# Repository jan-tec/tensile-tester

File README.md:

# Tensile Tester

ESP32 firmware for a tensile test machine (Zugversuchsmaschine): a
gear-stepper spindle with load-cell force measurement, an automated pull-to-
break test cycle with CSV data capture, a constant-force hold mode, and a
WiFi web UI plus serial CLI. English-first with a German locale switch
(`lang de` or the Web UI selector; persisted in NVS).

## Hardware

| Component | Model / value |
|-----------|---------------|
| MCU | ESP32 (PlatformIO board `esp32dev`) |
| Stepper driver | TMC2209, plain STEP/DIR/EN (shared STEP/DIR, EN1/EN2 per driver; no UART configuration wired) |
| Stepper motor | NEMA 17, 200 full steps/rev, x2 (run synchronously on the same signals) |
| Gearbox | 13.73:1 |
| Spindle pitch | 2 mm/rev |
| Load cell | HX711 ADC (YZC-516C) |

### Wiring

| Signal | GPIO | Notes |
|--------|------|-------|
| STEP | 18 | |
| DIR | 19 | |
| EN1 | 5 | motor 1 driver, active low (LOW = driver enabled) |
| EN2 | 23 | motor 2 driver, active low, switched together with EN1 |
| HX711 DOUT | 32 | |
| HX711 SCK | 33 | |
| Endstop 1 (bottom, datum) | 25 | `INPUT_PULLUP`, NC wiring (broken wire reads as pressed) |
| Endstop 2 (top, travel limit) | 26 | `INPUT_PULLUP`, NC wiring |
| Status LED | 2 | onboard LED, LEDC PWM, configured after boot selftest |
| 5 V rail sense | 34 | 10 k/10 k divider - **not built yet**, POWER check reads `NOT_WIRED` |

Mainboard CAD sources: `hardware/mainboard-atlas/` (KiCad 9).

## Requirements

- PlatformIO CLI: `pipx install platformio` (first build downloads the
  `espressif32` toolchain, ~200 MB)
- ESP32 dev board on USB for flashing

## Build and flash

```bash
pio run -e esp32dev            # build (only env)
pio run -t upload -e esp32dev  # flash
pio device monitor -p <port> -b 115200
```

Boot runs a selftest (BOARD, NVS, POWER, HX711, MOTOR, ENDSTOP1, ENDSTOP2)
and logs `BOOT`/`STATE`/`CHECK` lines; any FAIL locks the device in the
Error state with the driver off (recovery = reboot).

## Serial CLI (115200 baud)

Same command policy as the web API (`Commands::execute()`); unknown commands
print help. Replies are localized text; a JSON envelope (M6,
`lib/FirmwareCore/src/ApiResponse.h`) wraps replies and runner events for
host automation.

| Command | Effect |
|---------|--------|
| `en` / `off` | enable / disable both driver outputs |
| `zero` | set axis position to 0 |
| `tare` | tare the load cell |
| `pos` | print position (steps + mm) and force |
| `force` | print current force in N |
| `stop` | stop motion; aborts a running homing/test cycle first |
| `rpm <U/min>` | set gear output speed |
| `acc <U/min/s>` | set acceleration |
| `feed <mm/min>` | set spindle feed rate (clamped 0.5 - 60) |
| `move <mm>` | relative spindle move |
| `turn <revs>` | relative gear output rotation |
| `jog up` / `jog down` | continuous jog for a relative 1000 mm travel; stop with `stop` |
| `cal_zero` | calibration step 1 (load cell unloaded) |
| `cal_apply <grams>` | calibration step 2 with a known mass in grams |
| `home` / `home top` | staged homing to the bottom datum / move to the top limit |
| `test` | run the tensile test cycle (pull until break, capture samples) |
| `testspeed <mm/min>` | test/homing speed (persisted) |
| `testarm <N>` | break-detector arm threshold (persisted) |
| `testdrop <%>` | break criterion: force drop from peak (persisted) |
| `homeseek <mm/min>` | homing seek speed (0 = follow testspeed; persisted) |
| `hometimeout <s>` | homing seek timeout, 1-300 s (persisted) |
| `chold <N> [minutes]` | constant-force hold at N newtons, optional duration |
| `choltol <%>` | hold tolerance band in % of setpoint (persisted) |
| `choldclear <mm>` | hold approach clearance (persisted) |
| `choldmax <N>` | per-sample hold force ceiling, 1-4000 N (persisted) |
| `data [from-index]` | stream captured samples as CSV (resumable) |
| `testdata` | one-line sample/peak summary |
| `ends` | bench telemetry: endstops, homing phase, cycle state, hold phase |
| `lang <en\|de>` | UI locale (persisted) |

## Web UI

The ESP32 starts in WiFi **AP mode** (no client network needed):

- SSID: `ESP32-Testmaschine`, password: `testmaschine`
- UI at the softAP IP (default `192.168.4.1`; the actual IP is printed to
  serial and reported in `/api/status`)

The M7 UI is a monochrome, single-red-accent operator surface with one
global sticky Stop. The tear workflow is first-class: Home -> sample
prompt -> Start test -> run summary -> force-displacement curve -> CSV
download. It also carries the boot-selftest card, manual motion/calibration
controls, the test settings forms (testspeed/testarm/testdrop) and the
EN/DE selector. Hold visualization is view-only pending M4-T007.

API (all endpoints are GET):

| Endpoint | Payload |
|----------|---------|
| `/api/status` | JSON: driver/motion state, position/steps, force, calibration, `state` + `faultCode` + `selftest{overall,checks[]}`, cycle/homing/hold state, `network` |
| `/api/command?cmd=<command>` | executes a CLI command; returns `{"ok":bool,"message":"..."}` |
| `/api/data` | the run CSV, same grammar as the serial `data` dump; rejected while a cycle is active or a serial dump is in flight |

## Load cell calibration

1. Remove the load, run step 1 (`cal_zero` / "1. Unbelastet bestaetigen").
2. Hang a known mass, enter the mass in grams, run step 2
   (`cal_apply <grams>` / "2. Gewicht messen").

The calibration factor persists in NVS (Preferences namespace `testmachine`)
and is loaded automatically at the next boot. Force is displayed in newtons
(converted from grams with g = 9.80665 m/s^2). Which mass to use and why:
`docs/calibration.md` (calibrate near the working load).

## Motion math

| Parameter | Value |
|---------|-------|
| Motor full steps/rev | 200 |
| Gear ratio | 13.73 |
| Microsteps | 8 |
| Steps per spindle revolution | 21968 |
| Spindle pitch | 2 mm/rev |
| Feed clamp | 0.5 - 60 mm/min |

The constants live in `lib/FirmwareCore` (host-tested) - keep them in sync
if the gearbox, motor or spindle changes.

## Repository layout

| Path | Purpose |
|------|---------|
| `src/` | Firmware modules: composition root (`main.cpp`), `App` orchestration, `Commands`, `SerialCli`, `WebUi` + `UiHtml.h`, `Motion`, `LoadCell`, `Settings`, `Diagnostics`, `Endstops`, `PowerSense`, `TestRunner`, `LedStatus`, `Text` |
| `lib/FirmwareCore/` | Pure C++ (no Arduino): gear/feed math, command parser, state machines, homing/test/hold models, break detector, sample buffer + CSV, LED patterns, JSON envelope |
| `test/` | Unity host tests (`pio test -e native`) |
| `specs/` | Milestone specs, plans, task backlogs (`specs/README.md` is the roadmap) |
| `docs/` | Operator docs: calibration, LED patterns, power-rail check |
| `hardware/` | KiCad mainboard sources |
| `standalone_tests/` | Debug sketches - not built automatically |

### Running a standalone test

PlatformIO compiles everything in `src/`, so a debug sketch is NOT built
automatically. Swap it into `src/main.cpp` temporarily and never commit the
swapped state (details in AGENTS.md).

## Status

| Feature | State |
|---------|-------|
| Manual control (web UI + serial CLI) | done |
| Load cell measurement + persisted calibration | done |
| Boot selftest + Error state, i18n DE/EN, LED status language | done |
| Staged homing to a datum | done (bench-verified) |
| Automated pull-to-break test cycle + CSV capture | done (bench-verified) |
| Constant-force hold (`chold`, closed-loop) | firmware done; formal bench evidence open (M4-T008/T009) |
| Hold web view + buffer keep-last ring | open (M4-T007/T004) |
| Guided calibration wizard (M5) | open (manual `cal_zero`/`cal_apply` work) |
| 5 V rail divider hardware | open (POWER reads `NOT_WIRED`) |

## History and versioning

See [CHANGELOG.md](CHANGELOG.md). The project follows Semantic Versioning;
no release has been tagged yet (see `[Unreleased]`).

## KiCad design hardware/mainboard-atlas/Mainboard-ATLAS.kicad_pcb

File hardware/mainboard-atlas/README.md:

# Mainboard ATLAS - CAD sources

Custom carrier mainboard of the tensile test machine: ESP32 DevKit (2x15 header),
HX711 load-cell breakout, two TMC2209 stepper-driver breakouts, endstop and
load-cell connectors, 24 V -> 5 V / 3.3 V power.

## Board

| Property | Value |
|----------|-------|
| Size / stackup | 100 x 80 mm, 2 layers, 1.6 mm |
| Design rules | min track 0.25 mm, clearance 0.2 mm, min drill 0.8 mm |
| Net classes | `POWER_24V` 2.0 mm / `POWER_5V` 1.0 mm track width |
| Parts | 25 footprints, 120 pads (THT-heavy, ~46 % front density) |
| Holes | 115 PTH (0.8 - 1.3 mm), 5 NPTH (4x M3 + 1x 2.7 mm) |
| Validation | DRC 0 errors / 2 warnings / 0 unconnected, ERC clean |

## Provenance

- Board silkscreen stamp: `Mainboard v1.0 // 07/2026 // Jan Wegener`
  (v1.0, matches the July 2026 fab run). Title/company metadata:
  "Mainboard ATLAS" by JanTec Engineering.
- Imported 2026-10-10 from the designer's KiCad 9 project.
- Re-saved 2026-10-13 with KiCad 10.0.7 (format 20260206); DRC fingerprint
  unchanged by the migration.
- `gerber/` is the manufacturing output of record (2026-07-09 fab run, plotted
  with KiCad 9.0.7: copper/mask/silk/outline + drill; the package contains no
  paste layers). Do not re-plot - regenerate only for a new spin.

## Known issues (imported legacy)

- ~~Schematic <-> board annotation drift~~ **fixed 2026-10-13 (H1, spec
  `specs/H1-atlas-annotation-debt/`)**: board adopted the schematic references
  (J4/HX1/TMC1/TMC2, `//`-corrupted refs cleaned, mounting holes named
  H1..H4). Remaining parity findings: 4 `extra_footprint` entries for the
  board-only mounting holes (KiCad 10 has no suppression for those).
  Caveat: the built rev-1 boards carry the old corrupt silks
  (`C6 // 100nF`, `J1 // 24V IN`); only a re-spin prints the clean text -
  `gerber/` stays frozen as the as-built package.
- The 2 DRC warnings are the TMC2209 Pololu module footprints not matching the
  current KiCad 10 standard-library copy.
- Custom symbols/footprints carry no courtyard and no 3D models (they render
  as empty boards areas in the images above).

## Files

| File | Purpose |
|------|---------|
| `Mainboard-ATLAS.kicad_sch` | Main schematic (ENDSTOP1/ENDSTOP2 nets, power, HX711, drivers) |
| `Mainboard-ATLAS.kicad_pcb` | PCB layout |
| `Mainboard-ATLAS.kicad_pro` | Project settings, design rules, net classes |
| `Breakoutboards.kicad_sym` | Custom symbols (NodeMCU-ESP32, HX711, TMC2209) |
| `PEM.kicad_sym` | Unused leftover symbol lib (KY-040, LM2596, ...) from earlier experiments |
| `Breakoutboard-Footprints.pretty/` | Custom footprints (ESP32 header, HX711 breakout) |
| `fp-lib-table`, `sym-lib-table` | Library tables (`${KIPRJMOD}` relative refs) |
| `gerber/` | Fab package of record (see Provenance) |
| `validation-baseline.json` | Fingerprint ledger baseline (`tools/kicad-validation`) |
| `img/` | Board renders (`kicad-cli pcb render`, see below) |

## Headless tooling (no GUI needed)

```bash
kicad-cli pcb drc --severity-all --format json -o /tmp/drc.json Mainboard-ATLAS.kicad_pcb
kicad-cli sch erc --format json -o /tmp/erc.json Mainboard-ATLAS.kicad_sch
kicad-cli sch export netlist --format kicadsexpr Mainboard-ATLAS.kicad_sch -o /tmp/atlas.net
kicad-cli pcb render --side top --quality high -w 1600 -o top.jpg Mainboard-ATLAS.kicad_pcb
```

Programmatic edits go through `kicad-tools` (round-trip validated for this
format); the repo gate `tools/kicad-validation/kicad_validate.py` must stay
green after any change. `kiutils` cannot parse this file format - do not use it
on these files.

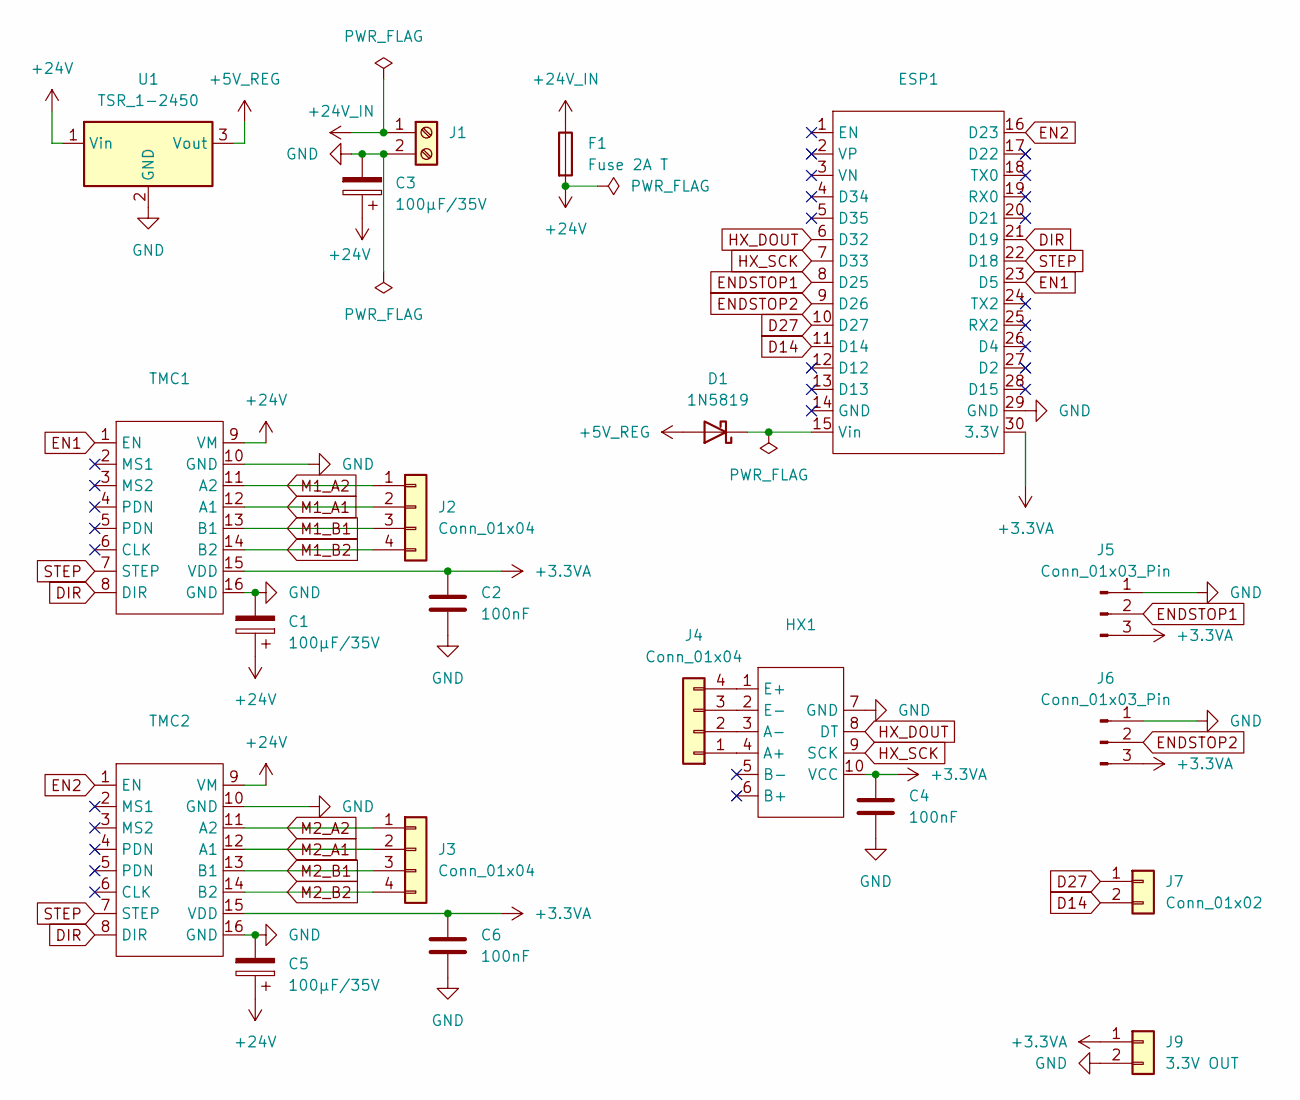
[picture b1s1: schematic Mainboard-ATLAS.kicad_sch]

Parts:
C1, C3, C5: 100µF/35V; CP_Radial_D8.0mm_P3.50mm
C2, C4, C6: 100nF; C_Disc_D5.0mm_W2.5mm_P5.00mm
D1: 1N5819; D_DO-41_SOD81_P10.16mm_Horizontal
ESP1: ESP32_2x15_P254_Row25
F1: Fuse 2A T; Fuseholder_Cylinder-5x20mm_Schurter_0031_8201_Horizontal_Op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
HX1: HX711-Breakout-6-4
J1: Screw_Terminal_01x02; TerminalBlock_Phoenix_MKDS-1,5-2_1x02_P5.00mm_Horizontal
J2, J3, J4: Conn_01x04; JST_XH_B4B-XH-A_1x04_P2.50mm_Vertical
J5, J6: Conn_01x03_Pin; JST_XH_B3B-XH-A_1x03_P2.50mm_Vertical
J7: Conn_01x02; PinHeader_1x02_P2.54mm_Vertical
J9: 3.3V OUT; PinHeader_1x02_P2.54mm_Vertical
TMC1, TMC2: Pololu_Breakout-16_15.2x20.3mm
U1: TSR_1-2450; Converter_DCDC_TRACO_TSR-1_THT

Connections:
+3.3VA: C2.1, C4.1, C6.1, ESP1.30 (3.3V), HX1.10 (VCC), J5.3, J6.3, J9.1, TMC1.15 (VDD), TMC2.15 (VDD)
+5V_REG: D1.2 (A), U1.3 (Vout)
+24V: C1.1, C3.1, C5.1, F1.2, TMC1.9 (VM), TMC2.9 (VM), U1.1 (Vin)
+24V_IN: F1.1, J1.1
D14: ESP1.11 (D14), J7.2
D27: ESP1.10 (D27), J7.1
DIR: ESP1.21 (D19), TMC1.8 (DIR), TMC2.8 (DIR)
EN1: ESP1.23 (D5), TMC1.1 (EN)
EN2: ESP1.16 (D23), TMC2.1 (EN)
ENDSTOP1: ESP1.8 (D25), J5.2
ENDSTOP2: ESP1.9 (D26), J6.2
GND: C1.2, C2.2, C3.2, C4.2, C5.2, C6.2, ESP1.29 (GND), HX1.7 (GND), J1.2, J5.1, J6.1, J9.2, TMC1.10 (GND), TMC1.16 (GND), TMC2.10 (GND), TMC2.16 (GND), U1.2 (GND)
HX_DOUT: ESP1.6 (D32), HX1.8 (DT)
HX_SCK: ESP1.7 (D33), HX1.9 (SCK)
M1_A1: J2.2, TMC1.12 (A1)
M1_A2: J2.1, TMC1.11 (A2)
M1_B1: J2.3, TMC1.13 (B1)
M1_B2: J2.4, TMC1.14 (B2)
M2_A1: J3.2, TMC2.12 (A1)
M2_A2: J3.1, TMC2.11 (A2)
M2_B1: J3.3, TMC2.13 (B1)
M2_B2: J3.4, TMC2.14 (B2)
unnamed: D1.1 (K), ESP1.15 (Vin)
unnamed: HX1.4 (A+), J4.1
unnamed: HX1.3 (A-), J4.2
unnamed: HX1.1 (E+), J4.4
unnamed: HX1.2 (E-), J4.3
STEP: ESP1.22 (D18), TMC1.7 (STEP), TMC2.7 (STEP)

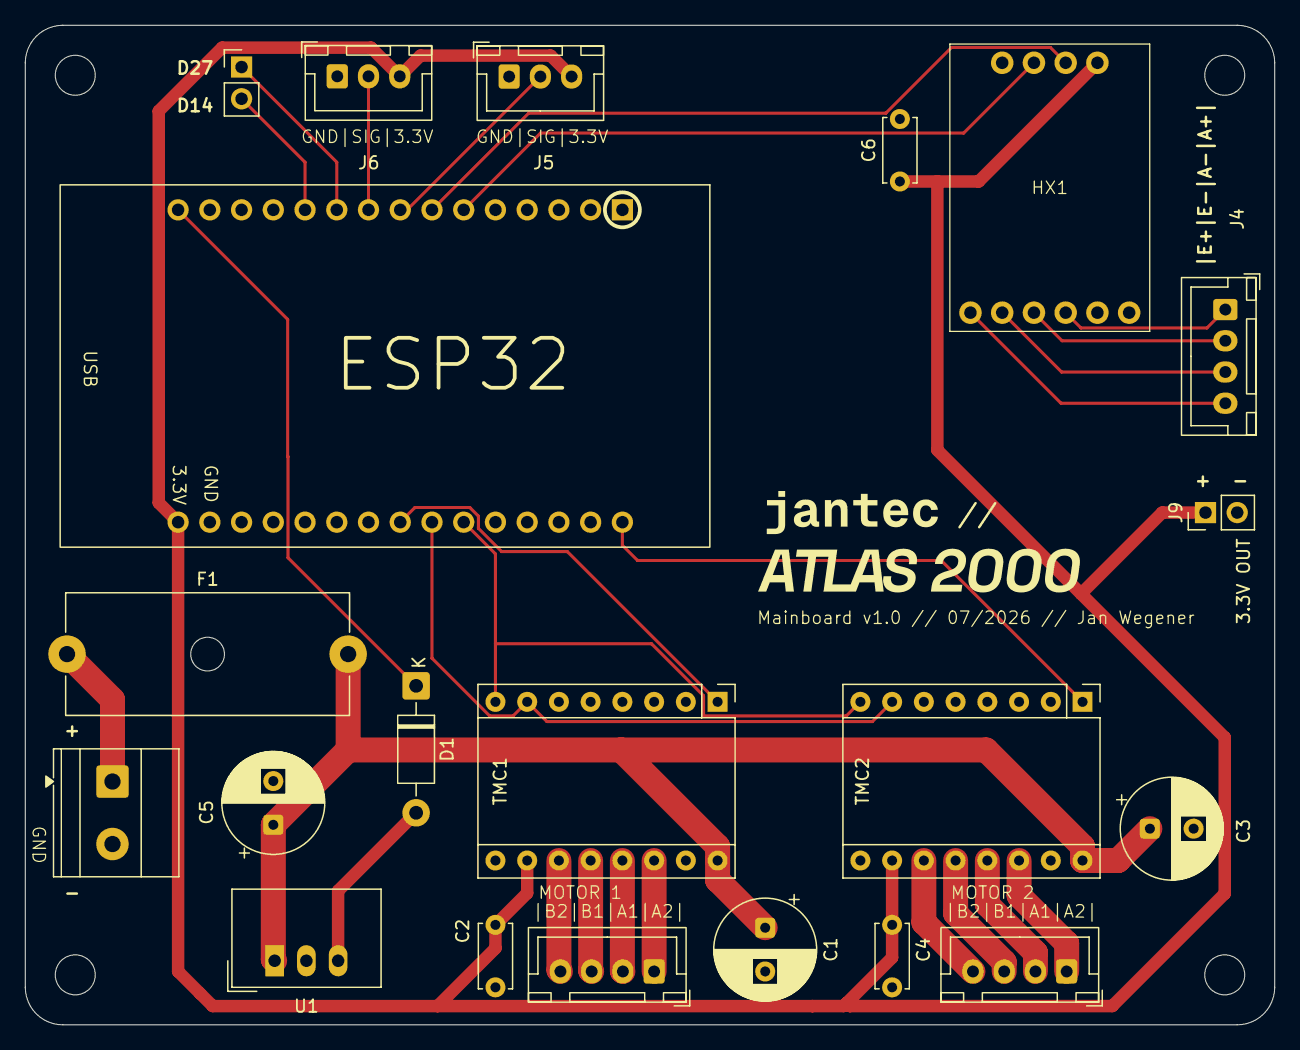
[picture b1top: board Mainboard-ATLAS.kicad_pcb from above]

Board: 2 copper layers, 100.0 x 80.0 mm, 25 parts (0 on the bottom side), 28 nets.

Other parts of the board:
H1, H2, H3, H4: MountingHole_3.2mm_M3

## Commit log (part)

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2026-04-12 Initial PlatformIO commit
2026-04-12 initalized
2026-04-12 added test files for blink and loadcell raw
2026-04-12 added menu for calibration and measurement with loadcell - not tested yet
2026-04-13 added move motor function
2026-04-13 added web interface for testing
2026-04-14 Added Calibration to Web Interface
